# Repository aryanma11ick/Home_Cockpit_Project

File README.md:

# 🛫 Home Cockpit System

A custom-built **modular home cockpit system** for flight simulation, focused on replicating real aircraft controls using **PCB design, CAD modeling, and embedded systems**.

This project combines **hardware engineering + software integration** to create a scalable and realistic cockpit environment.

---

## ✈️ Overview

The goal of this project is to design a **high-fidelity, modular cockpit system** that closely mimics real aircraft panels while remaining flexible for expansion.

Key design principles:

* 🔧 **Modularity** – Panels can be developed and used independently
* 🧩 **Scalability** – Easy to expand into a full cockpit
* 🎯 **Realism** – Accurate switch behavior and layout
* ⚡ **Integration** – Seamless connection with flight simulators

---

## 🧱 Project Structure

```text
hardware/
├── pcb/          # KiCad design files + Gerbers
└── cad/          # STEP/STL files for panels and components

firmware/         # Microcontroller code (Arduino / ESP32)

software/         # Simulator interface plugins (X-Plane, etc.)

docs/             # Documentation, diagrams, and images
```

---

## 🔧 Modules

### 🟢 Overhead External Lights Panel

* Fully functional external lighting control panel
* Supports multiple 3-position and 2-position switches
* Integrated with simulator via custom plugin
* Designed for real-time hardware ↔ simulator synchronization

---

### 🟡 Annunciator (Alert) Panel

* Displays aircraft alerts and system states
* Uses custom illuminated switches
* Modular layout for future expansion

---

### 🔘 Korry Switch Module (v2)

* Custom PCB designed in KiCad
* LED backlighting support
* Reusable module for multiple panels
* Includes CAD models for enclosure and mounting

---

## ⚙️ Technologies Used

### 🧠 Hardware

* **KiCad** – PCB design and layout
* **Fusion 360 / CAD tools** – Mechanical design and panel modeling

### 💻 Software

* **C++ (X-Plane SDK)** – Simulator interface plugins
* **Arduino / ESP32** – Firmware and hardware control

### 🔗 Tools

* **GitHub** – Version control and project management

---

## 🔁 System Architecture

```text
[Physical Switches] → [Microcontroller] → [Serial Communication]
                                  ↓
                            [Plugin / Interface]
                                  ↓
                             [Flight Simulator]
                                  ↑
                          [DataRef Feedback Loop]
```

* Closed-loop system ensures **hardware and simulator stay synchronized**
* Supports **real-time control and feedback**

---

## 🚧 Project Status

**Status:** 🟢 Active Development

### ✅ Completed

* Korry Switch PCB (v2)
* Initial CAD panel designs
* Overhead external lights panel (hardware + integration)

### 🔄 In Progress

* Firmware refinement
* Panel integration and wiring
* Simulator interface improvements

---

## 📸 Media

### Hardware Preview

---

## 🚀 Future Plans

* Enhanced backlighting and light diffusion
* Full overhead panel completion
* Additional cockpit modules (FCU, MCDU, etc.)
* Improved simulator integration and feedback systems
* Expansion to a complete cockpit build

---

## 👤 Author

**Aryan Mallick**
Building a full-scale home cockpit system from scratch

---

## ⭐ Notes

This project is continuously evolving with improvements in:

* Hardware design
* Firmware reliability
* Simulator integration

Contributions, suggestions, and feedback are welcome.

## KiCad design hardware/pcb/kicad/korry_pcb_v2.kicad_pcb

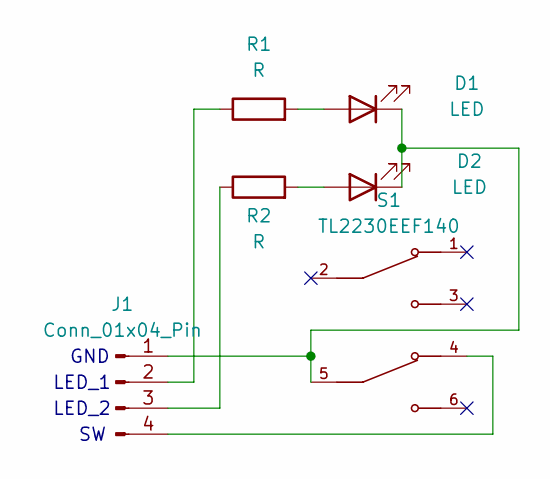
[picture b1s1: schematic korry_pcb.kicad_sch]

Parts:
D1, D2: LED; LED_Rectangular_W5.0mm_H2.0mm
J1: Conn_01x04_Pin; PinHeader_1x04_P2.54mm_Vertical
R1, R2: R; R_0805_2012Metric_Pad1.20x1.40mm_HandSolder
S1: TL2230EEF140; SW_TL2230EEF140; PARTREV E

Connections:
unnamed: D1.2 (A), R1.2
unnamed: D1.1 (K), D2.1 (K), J1.1, S1.5
unnamed: D2.2 (A), R2.2
unnamed: J1.2, R1.1
unnamed: J1.3, R2.1
unnamed: J1.4, S1.4

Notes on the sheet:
LED_2
LED_1
GND

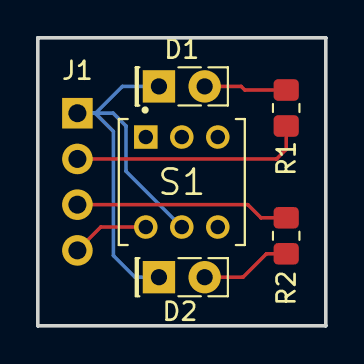
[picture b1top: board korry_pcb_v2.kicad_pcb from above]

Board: 2 copper layers, 16.0 x 16.0 mm, 6 parts (1 on the bottom side), 6 nets.

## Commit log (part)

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2026-04-07 Create docs folder
2026-04-07 Create Images folder under docs
2026-04-07 gerber files for the korry buttons pcb
2026-04-07 KiCad Files of the Korry Buttons PCB
2026-04-07 Korry Button PCB 3D Model
2026-04-07 Rename korry_switch_pcb_gerber-v3.zip to korry_switch_pcb_gerber.zip
2026-04-07 Rename Korry PCB file to korry_pcb.kicad_pcb
2026-04-07 Rename korry_pcb_v2.kicad_prl to korry_pcb.kicad_prl
2026-04-07 Rename korry_pcb_v2.kicad_pro to korry_pcb.kicad_pro
2026-04-07 Rename korry_pcb_v2.kicad_sch to korry_pcb.kicad_sch
2026-04-07 Rename korry_pcb_v2.step to korry_pcb.step
2026-04-09 Korry Switch KiCad Files
2026-04-09 Rename Alert_Top_Panel_v2.rld to Alert_Top_Panel.rld
2026-04-09 Rename alert_top_panel_v2.rd to alert_top_panel.rd
2026-04-09 Create ovhd_ext_lights_panel
2026-04-09 Rename hardware/cad/step/korry_pcb.step to hardware/cad/step/korry_button/korry_pcb.step
2026-04-09 Add initial README for home cockpit system project
    This README introduces a custom-built home cockpit system for flight simulation, detailing project goals, structure, completed modules, technologies used, project status, and future plans.
2026-04-09 Fix formatting in project structure section of README
2026-04-17 Update documentation for ToLiss A320Neo panel
2026-04-17 Update image formats and improve notes section
2026-04-17 Refactor serial communication for light and alert handling
